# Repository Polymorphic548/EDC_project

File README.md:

# Diode-Compensated Current Mirror PCB

A single-sided PCB containing two independent, diode-compensated 2N3904 current mirrors. This repository includes the original LTspice circuit, KiCad schematic and layout, assembly drawings, and matched Gerber and drill files.

Each circuit has a power connector and three voltage-measurement headers: across the load and across each transistor's base and emitter.

| Specification | Design |
|---|---|
| Panel size / thickness | 150 x 100 mm / 1.7 mm |
| Circuits | Two electrically isolated copies, A and B |
| Copper | Single-sided, B.Cu |
| Track width / configured minimum clearance | 0.6 mm / 0.8 mm |
| Supply | 9.8 V DC per circuit |
| Assembly | Through-hole; 36 footprints including eight 2-pin headers |
| Header pitch | 2.54 mm |
| Adjustment resistor | Fixed 120 ohm; no trimmer |
| Software | KiCad 10.0.7 or later |

The saved design and exports pass the recorded CAD and geometry checks. **The rectangular-pad export still requires confirmation in the lab's CopperCAM installation.** Physical circuit performance has not been measured.

## Open the design

1. Open [dual_current_mirror.kicad_pro](PCB%20layout/dual_current_mirror.kicad_pro) in KiCad.
2. Open [dual_current_mirror.kicad_pcb](PCB%20layout/dual_current_mirror.kicad_pcb) in PCB Editor.
3. Press **Alt+3** for the 3D Viewer.

The [single-circuit project](PCB%20layout/current_mirror.kicad_pro) is a reusable 78 x 67 mm unit. Use the **dual** project for the complete panel.

[Copper preview](PCB%20layout/previews/dual_panel_copper_review.png) | [Panel schematic PDF](PCB%20layout/previews/dual_panel_schematic.pdf)

The supplied KiCad screenshot below shows the current placement and routing before the rectangular-pad update. The generated drawing above shows the current pads.

## Circuit and components

The input passes through a 1 ohm resistor and a series 1N4007 diode. A Zener and two signal diodes provide the compensation network. Each transistor has a 22 ohm emitter resistor, and the output drives a 1 kohm load. The LTspice parameterized resistor RV1 is implemented as fixed R7/R107, nominally 120 ohm.

| Copy A | Copy B | Component / value |
|---|---|---|
| R1 | R101 | 1 ohm, 1/4 W input resistor |
| R2 | R102 | 662 ohm, 1/4 W |
| R3 | R103 | 1 kohm, 1/4 W |
| R4, R5 | R104, R105 | 22 ohm, 1/4 W emitter resistors |
| R6 | R106 | 1 kohm, 1/4 W load |
| R7 | R107 | Fixed 120 ohm, 1/4 W |
| D1, D2 | D101, D102 | 1N4148 |
| D3 | D103 | BZX55C5V1, 5.1 V Zener |
| D4 | D104 | 1N4007 |
| Q1, Q2 | Q101, Q102 | 2N3904 |
| C1 | C101 | 1.33 nF, at least 25 V |
| J1-J4 | J101-J104 | Four 1x2 male headers, 2.54 mm pitch |

See the [panel BOM](PCB%20layout/panel_BOM.csv) for the complete assembly list. Two populated circuits require two sets of parts and eight headers total. R1 is a resistor, not a fuse.

The original nominal 120 ohm resistor measured 117.6 ohm; measure the second circuit's resistor separately. The supplied LTspice results report approximately **4.625 mA at 25 degrees C** and **4.667 mA at 75 degrees C** with RV=117.6 ohm. These are source simulation results, not PCB measurements.

## Power and measurements

| Connection | Copy A | Copy B | Pin 1: positive / red | Pin 2: negative / black |
|---|---|---|---|---|
| Power input | J1 | J101 | VIN, +9.8 V | GND |
| Load voltage | J2 | J102 | VCC | OUT |
| First transistor VBE | J3 | J103 | BASE | E1 |
| Second transistor VBE | J4 | J104 | BASE | E2 |

Use **DC voltage mode**, with meter leads in COM and V/ohm. The circuit operates normally without a meter. These connectors must not be fitted with shorting caps.

VCC is the internal supply after the input resistor and diode. E1 and E2 are separate emitter nodes above their 22 ohm resistors; neither is ground. Copy B's transistors are Q101 and Q102.

Calculate output current using `Iout = Vload / Rload`. With a 1 kohm load, 5.00 V corresponds to 5.00 mA.

The circuits share no PCB nets, including ground. A common external supply or common-ground instrument can connect them externally.

## Fabrication

Use [dual_panel_machine_files.zip](PCB%20layout/fabrication/dual_panel_machine_files.zip) for the lab handoff. The [rectangle-pad package](PCB%20layout/fabrication/dual_panel_coppercam_rectangles.zip) contains identical files under a distinct name for a fresh CopperCAM import.

| File inside the package | Purpose |
|---|---|
| `dual_current_mirror-B_Cu.gbr` | Copper to retain; the only copper layer |
| `dual_current_mirror.drl` | Excellon drill locations and sizes |
| `dual_current_mirror-Edge_Cuts.gbr` | Optional outer 150 x 100 mm outline |
| `dual_current_mirror-Centre_Cut.gbr` | Optional straight centre separation line |

The package also contains a drill map, tool report, setup data, verification results and checksums. All geometry uses millimetres and a shared absolute origin. Apply fixture mirroring or positioning consistently to all layers. Through-hole pads may appear on F.Cu in KiCad, but only the **bottom copper pattern** is fabricated.

Extract into a fresh folder and open the copper Gerber in a new CopperCAM circuit. Before calculating contours, confirm that all three rectangular pads on each of the four transistors are visible. Import the drill file and verify that every hole aligns with its pad; the lab previously achieved registration using layers 1 and 5. Inspect the calculated isolation paths before machining. The copper export uses only standard circle and rectangle pad apertures.

### Centre separation

The optional centreline runs at **x=75 mm** across the panel. A centred 0.8 mm cutter leaves nominal **74.6 x 100 mm** halves without outer trimming.

[Centre-cut setup data](PCB%20layout/centre_cut_setup.json) records a **Roland monoFab SRM-20**, 1.7 mm board, 0.8 mm cutting diameter and maximum 0.4 mm depth per pass. **No executable cutting program is included.** The operator must confirm feeds, spindle speed, safe Z, zero reference, cutter suitability, breakthrough allowance, work holding and output format. Secure both halves and complete isolation and drilling before separation.

### Printed masks

[Unmirrored copper PDF](PCB%20layout/fabrication/dual_panel_BCu_unmirrored_1to1.pdf) | [Mirrored copper PDF](PCB%20layout/fabrication/dual_panel_BCu_mirrored_1to1.pdf)

For transfer or photoresist fabrication, confirm orientation and exposure polarity with the lab. Print at **100% / Actual Size** and measure the **50 mm calibration line**. Black denotes copper to retain. Transfer only the board area; calibration marks sit outside it. Assembly and review drawings are not fabrication masks.

## Assembly

Fit components on the face opposite the copper and solder on the copper side. There is no solder mask; use controlled amounts of flux-cored solder and inspect nearby joints for bridges.

- Verify the actual transistor manufacturer's pinout. CAD numbering is **1=emitter, 2=base, 3=collector**.
- All transistor and header pads are rectangular: **pad shape does not identify pin 1**. Follow numbering and assembly labels.
- Confirm physical fit: resistor pitch 7.62 mm, capacitor pitch 5 mm, transistor and header pitch 2.54 mm.
- Header holes are 1.0 mm; transistor holes are 0.8 mm. The panel also has 1.1 mm diode holes.
- Check diode polarity and power-connector orientation before applying power.

## Repository guide

| Location | Contents |
|---|---|
| [schematics/](schematics/) | Original LTspice schematic and related source files |
| [PCB layout/](PCB%20layout/README.md) | KiCad projects, BOMs and technical documentation |
| [Project.pretty/](PCB%20layout/Project.pretty/) | Shared project-local footprints |
| [previews/](PCB%20layout/previews/) | Assembly, schematic and copper review drawings |
| [fabrication/](PCB%20layout/fabrication/) | Machine packages and 1:1 masks |
| [reports/](PCB%20layout/reports/) | CAD checks, geometry audits and revision records |
| [scripts/](PCB%20layout/scripts/) | Design generation, export and verification utilities |

Recorded checks report zero ERC/DRC violations, zero unconnected items and zero schematic-parity issues for both projects under their configured rules. Independent audits verify isolated A/B nets, header connections, pad-to-netlist agreement and matching export geometry: **76 pads, 76 holes and 100 panel track segments**.

[Panel audit](PCB%20layout/reports/panel_audit.json) | [Export verification](PCB%20layout/fabrication/machine_files/verification.json) | [Pad audit](PCB%20layout/reports/coppercam_pads.json)

These checks establish saved-file consistency. Lab import, toolpaths, machining and physical circuit performance require verification on the actual equipment. Earlier revision records remain in `reports/`.

## License

This project is licensed under the [MIT License](LICENSE).

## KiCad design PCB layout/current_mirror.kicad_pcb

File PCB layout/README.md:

# PCB Design and Manufacturing Guide

This directory contains the KiCad implementation of the diode-compensated current mirror: a reusable circuit and a 150 x 100 mm panel containing two isolated copies. See the [project overview](../README.md) for component values and measurement instructions.

## Projects and previews

| Project | Purpose | Board size |
|---|---|---|
| [dual_current_mirror.kicad_pro](dual_current_mirror.kicad_pro) | Complete panel for fabrication | 150 x 100 mm |
| [current_mirror.kicad_pro](current_mirror.kicad_pro) | Reusable single circuit | 78 x 67 mm |

Open with **KiCad 10.0.7 or later**. Open the PCB in PCB Editor and press **Alt+3** for 3D. Both projects use [Project.pretty](Project.pretty/) through the supplied `fp-lib-table`. Reopen files from disk after external edits to avoid saving an older editor copy over them.

[Assembly PDF](previews/dual_panel_assembly.pdf) | [Copper review](previews/dual_panel_copper_review.png) | [Schematic PDF](previews/dual_panel_schematic.pdf)

The supplied screenshot shows the current placement and routing before the rectangular-pad update. The generated previews show the current pad outlines.

## Board construction

| Parameter | Specification |
|---|---|
| Physical copper / thickness | Single-sided B.Cu / 1.7 mm |
| Tracks | 0.6 mm; horizontal, vertical and 45 degrees sections |
| Configured minimum different-net clearance | 0.8 mm |
| Vias / jumpers / pours | None |
| Footprints / nets | 36 / 24 |
| Pad shapes | 36 rectangular, 40 circular |
| Holes | 56 x 0.8 mm; 16 x 1.0 mm; 4 x 1.1 mm |

Each unit is rotated 90 degrees, occupying 67 x 78 mm. Copy A's unit rectangle spans x=5.5-72.5 mm, y=11-89 mm; copy B spans x=77.5-144.5 mm, y=11-89 mm. The unit rectangles have a 5 mm gap.

Copy B adds 100 to the references: Q1 -> Q101, J1 -> J101, etc. All A/B nets are separate, including ground. Shared external supplies or instruments can connect them externally.

Only the outer boundary is on Edge.Cuts. The centre separation line is on User.1 and exports separately. Through-hole pads appear on both copper layers in KiCad's data model; all routing and fabrication copper artwork are B.Cu.

## Headers and footprints

All eight connectors are 1x2 male headers, 2.54 mm pitch. Use female jumper leads for power and instruments.

| Function | Copy A / B | Pin 1 | Pin 2 |
|---|---|---|---|
| 9.8 V power | J1 / J101 | VIN | GND |
| Load voltage | J2 / J102 | VCC | OUT |
| First transistor VBE | J3 / J103 | BASE | E1 |
| Second transistor VBE | J4 / J104 | BASE | E2 |

Use DC volts with red on pin 1 and black on pin 2. Emitters are separate nodes above their 22 ohm resistors. Do not fit shorting caps.

In the single-unit orientation, transistor pads are 1.7 x 2.4 mm with 0.8 mm holes; header pads are 2.4 x 1.7 mm with 1.0 mm holes. Both have 2.54 mm pitch and a 0.84 mm adjacent-pad gap. Panel rotation swaps the X/Y dimensions.

All transistor and header pads are rectangular. Identify pins by numbering and assembly labels, not pad shape. Transistor numbering is **1=E, 2=B, 3=C**; check the actual manufacturer's pinout. Confirm lead forming, resistor pitch of 7.62 mm and C1's assumed 5 mm lead spacing before fabrication.

[Panel BOM](panel_BOM.csv) | [Panel component/net data](panel_components.json) | [Unit BOM](BOM.csv)

## Machine handoff

Use [dual_panel_machine_files.zip](fabrication/dual_panel_machine_files.zip). The separately named [dual_panel_coppercam_rectangles.zip](fabrication/dual_panel_coppercam_rectangles.zip) contains identical files for the fresh import check.

| File | Import as |
|---|---|
| `dual_current_mirror-B_Cu.gbr` | Copper to retain |
| `dual_current_mirror.drl` | Excellon drilling data |
| `dual_current_mirror-Edge_Cuts.gbr` | Optional outer outline |
| `dual_current_mirror-Centre_Cut.gbr` | Optional centreline separation cut |

All files use millimetres, absolute coordinates and a shared unmirrored origin. Apply machine-side positioning or mirroring consistently to copper, drilling and cutting. No front-copper file is required. These files are CAM inputs; the operator generates executable machine output.

For CopperCAM:

1. Extract into a fresh folder and start a new circuit with the copper Gerber.
2. Before calculating contours, verify all three pads on each of Q1, Q2, Q101 and Q102, plus the header and diode pads.
3. Import the drill file and check every hole against its pad centre. The lab previously resolved registration using layers 1 and 5.
4. Inspect the calculated isolation paths for intact pads and connections before machining.

The export contains only standard circle/rectangle pad apertures, without oval pads, rounded rectangles, aperture macros or filled pad regions. **The rectangular-pad version still requires import confirmation in the lab's CopperCAM installation.**

### Centre separation

The centre-cut file contains one straight line at x=75 mm, y=0-100 mm in board coordinates. Import it as a separate centreline cutting operation, preserving alignment with the copper. It is not a closed outline or copper artwork.

[centre_cut_setup.json](centre_cut_setup.json) records the SRM-20, 1.7 mm board, 0.8 mm cutter diameter and maximum 0.4 mm pass depth. Nominal planning depths to board bottom are 0.4, 0.8, 1.2, 1.6 and 1.7 mm.

No executable RML/G-code or tabs are included. The operator must confirm feeds, spindle speed, safe Z, Z-zero, cutter type/usable length, holding, breakthrough allowance and output format. Secure both halves over a suitable sacrificial board and complete isolation and drilling before separation. A centred 0.8 mm kerf leaves nominal 74.6 x 100 mm halves without outer trimming.

### Printed masks

[Unmirrored 1:1 PDF](fabrication/dual_panel_BCu_unmirrored_1to1.pdf) | [Mirrored 1:1 PDF](fabrication/dual_panel_BCu_mirrored_1to1.pdf)

These contain B.Cu only; black denotes copper to keep. Confirm transfer orientation and exposure polarity with the lab. Print at Actual Size / 100%, measure the 50 mm calibration line and transfer only the board area. Review drawings are not masks. See [printing instructions](fabrication/PRINTING_README.md).

## Verification records

Recorded native checks report zero ERC/DRC violations, zero unconnected items and zero schematic-parity issues under the configured rules. Independent audits cover component values, netlist-to-pad agreement, header roles, unique identifiers, isolation, clearances and all 76 pad/drill locations.

| Record | Scope |
|---|---|
| [Panel audit](reports/panel_audit.json) | Dimensions, isolated nets and component mapping |
| [Panel ERC](reports/panel_erc.json) / [DRC](reports/panel_drc.json) | Native KiCad checks |
| [Source connectivity](reports/source_connectivity.json) | LTspice topology comparison |
| [Solder clearance](reports/solder_clearance.json) | Pad gaps and annular copper |
| [Pad audit](reports/coppercam_pads.json) | Rectangular transistor pads and Gerber apertures |
| [Export verification](fabrication/machine_files/verification.json) | Copper/drill geometry and cutting files |
| [Panel hashes](reports/panel_sha256.json) | Design and print-artifact integrity |

The reports establish saved-file consistency, not machining or electrical performance. Original LTspice files are preserved. The PCB uses fixed nominal 120 ohm resistors; the original source used RV=117.6 ohm. Earlier revision reports and trimmer templates are historical records.

## Maintenance

The [scripts](scripts/) include generators, routing, exports and checks. KiCad's bundled Python supplies `pcbnew`; PNG preview rendering uses regular Python with PyMuPDF. Some source checks also read installed LTspice symbols.

Treat the saved CAD files as the handoff design. Back up manual edits before running generators or the router: they rebuild geometry and may replace the saved placement or routing. After CAD changes, regenerate the relevant netlists, ERC/DRC/parity reports, audits, previews and manufacturing exports before packaging a new ZIP.

`export_machine_files.ps1` exports machine files; `check_machine_files.py` compares them with the board and writes verification/checksum records. Package those checked files together. Documentation-only edits do not require regeneration of manufacturing artifacts.

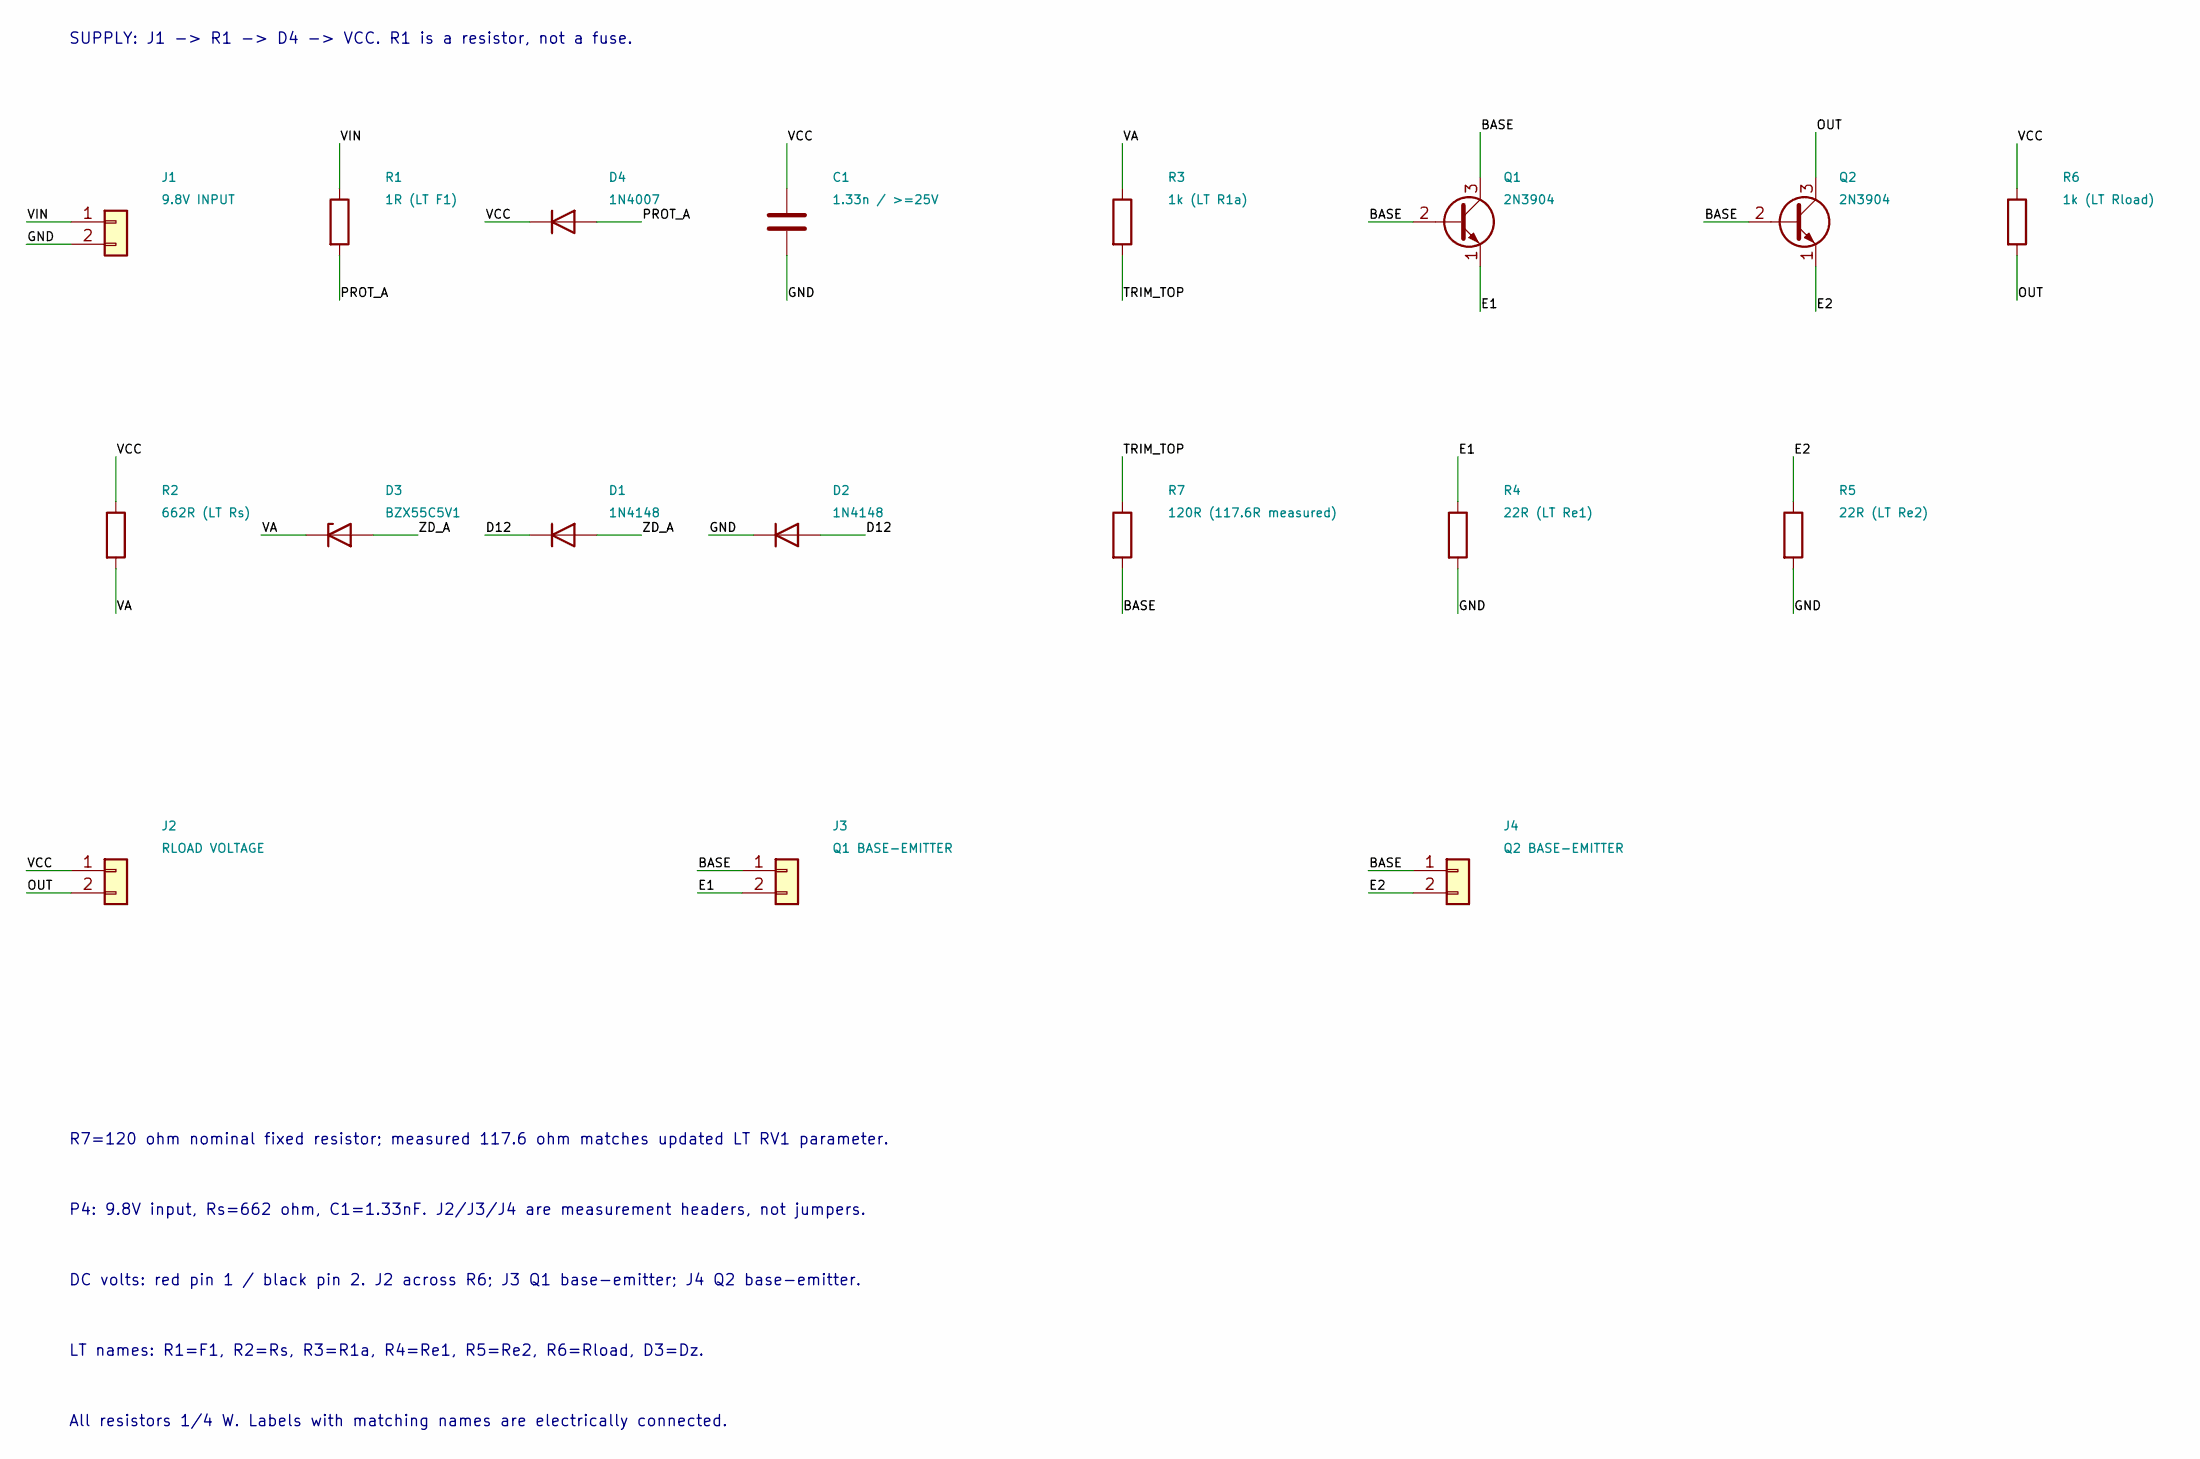
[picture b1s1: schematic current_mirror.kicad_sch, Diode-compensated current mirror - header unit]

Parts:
C1: 1.33n / >=25V; C1_ETCH
D1: 1N4148; D1_ETCH
D2: 1N4148; D2_ETCH
D3: BZX55C5V1; D3_ETCH
D4: 1N4007; D4_ETCH
J1: 9.8V INPUT; J1_ETCH
J2: RLOAD VOLTAGE; J2_ETCH
J3: Q1 BASE-EMITTER; J3_ETCH
J4: Q2 BASE-EMITTER; J4_ETCH
Q1: 2N3904; Q1_ETCH
Q2: 2N3904; Q2_ETCH
R1: 1R (LT F1); R1_ETCH
R2: 662R (LT Rs); R2_ETCH
R3: 1k (LT R1a); R3_ETCH
R4: 22R (LT Re1); R4_ETCH
R5: 22R (LT Re2); R5_ETCH
R6: 1k (LT Rload); R6_ETCH
R7: 120R (117.6R measured); R7_ETCH

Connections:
/BASE: J3.1, J4.1, Q1.2 (B), Q1.3 (C), Q2.2 (B), R7.2
/D12: D1.1 (K), D2.2 (A)
/E1: J3.2, Q1.1 (E), R4.1
/E2: J4.2, Q2.1 (E), R5.1
/GND: C1.2, D2.1 (K), J1.2, R4.2, R5.2
/OUT: J2.2, Q2.3 (C), R6.2
/PROT_A: D4.2 (A), R1.2
/TRIM_TOP: R3.2, R7.1
/VA: D3.1 (K), R2.2, R3.1
/VCC: C1.1, D4.1 (K), J2.1, R2.1, R6.1
/VIN: J1.1, R1.1
/ZD_A: D1.2 (A), D3.2 (A)

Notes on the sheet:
SUPPLY: J1 -> R1 -> D4 -> VCC. R1 is a resistor, not a fuse.
R7=120 ohm nominal fixed resistor; measured 117.6 ohm matches updated LT RV1 parameter.
P4: 9.8V input, Rs=662 ohm, C1=1.33nF. J2/J3/J4 are measurement headers, not jumpers.
DC volts: red pin 1 / black pin 2. J2 across R6; J3 Q1 base-emitter; J4 Q2 base-emitter.
LT names: R1=F1, R2=Rs, R3=R1a, R4=Re1, R5=Re2, R6=Rload, D3=Dz.
All resistors 1/4 W. Labels with matching names are electrically connected.

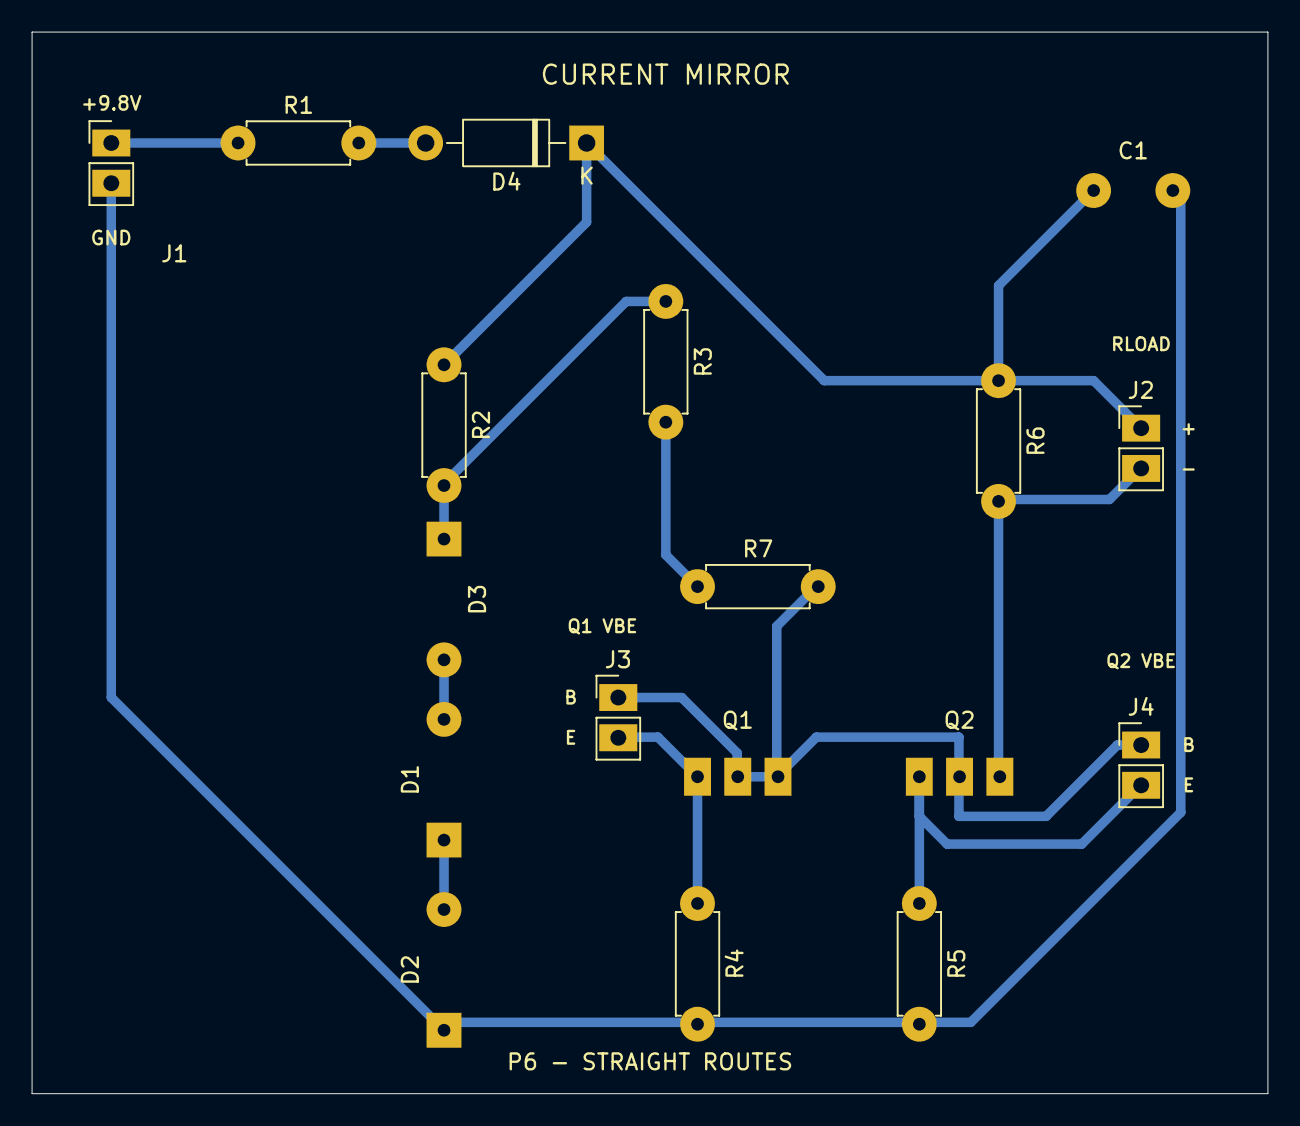
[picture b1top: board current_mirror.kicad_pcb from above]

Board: 2 copper layers, 78.0 x 67.0 mm, 18 parts (0 on the bottom side), 12 nets.

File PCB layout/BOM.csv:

Reference,Value,Footprint,Status
J1,9.8V INPUT,Project:J1_ETCH,package assumption - confirm physical part
R1,1R (LT F1),Project:R1_ETCH,package assumption - confirm physical part
D4,1N4007,Project:D4_ETCH,package assumption - confirm physical part
C1,1.33n / >=25V,Project:C1_ETCH,package assumption - confirm physical part
R2,662R (LT Rs),Project:R2_ETCH,package assumption - confirm physical part
D3,BZX55C5V1,Project:D3_ETCH,package assumption - confirm physical part
D1,1N4148,Project:D1_ETCH,package assumption - confirm physical part
D2,1N4148,Project:D2_ETCH,package assumption - confirm physical part
R3,1k (LT R1a),Project:R3_ETCH,package assumption - confirm physical part
R7,120R (117.6R measured),Project:R7_ETCH,package assumption - confirm physical part
Q1,2N3904,Project:Q1_ETCH,package assumption - confirm physical part
Q2,2N3904,Project:Q2_ETCH,package assumption - confirm physical part
R4,22R (LT Re1),Project:R4_ETCH,package assumption - confirm physical part
R5,22R (LT Re2),Project:R5_ETCH,package assumption - confirm physical part
R6,1k (LT Rload),Project:R6_ETCH,package assumption - confirm physical part
J2,RLOAD VOLTAGE,Project:J2_ETCH,package assumption - confirm physical part
J3,Q1 BASE-EMITTER,Project:J3_ETCH,package assumption - confirm physical part
J4,Q2 BASE-EMITTER,Project:J4_ETCH,package assumption - confirm physical part

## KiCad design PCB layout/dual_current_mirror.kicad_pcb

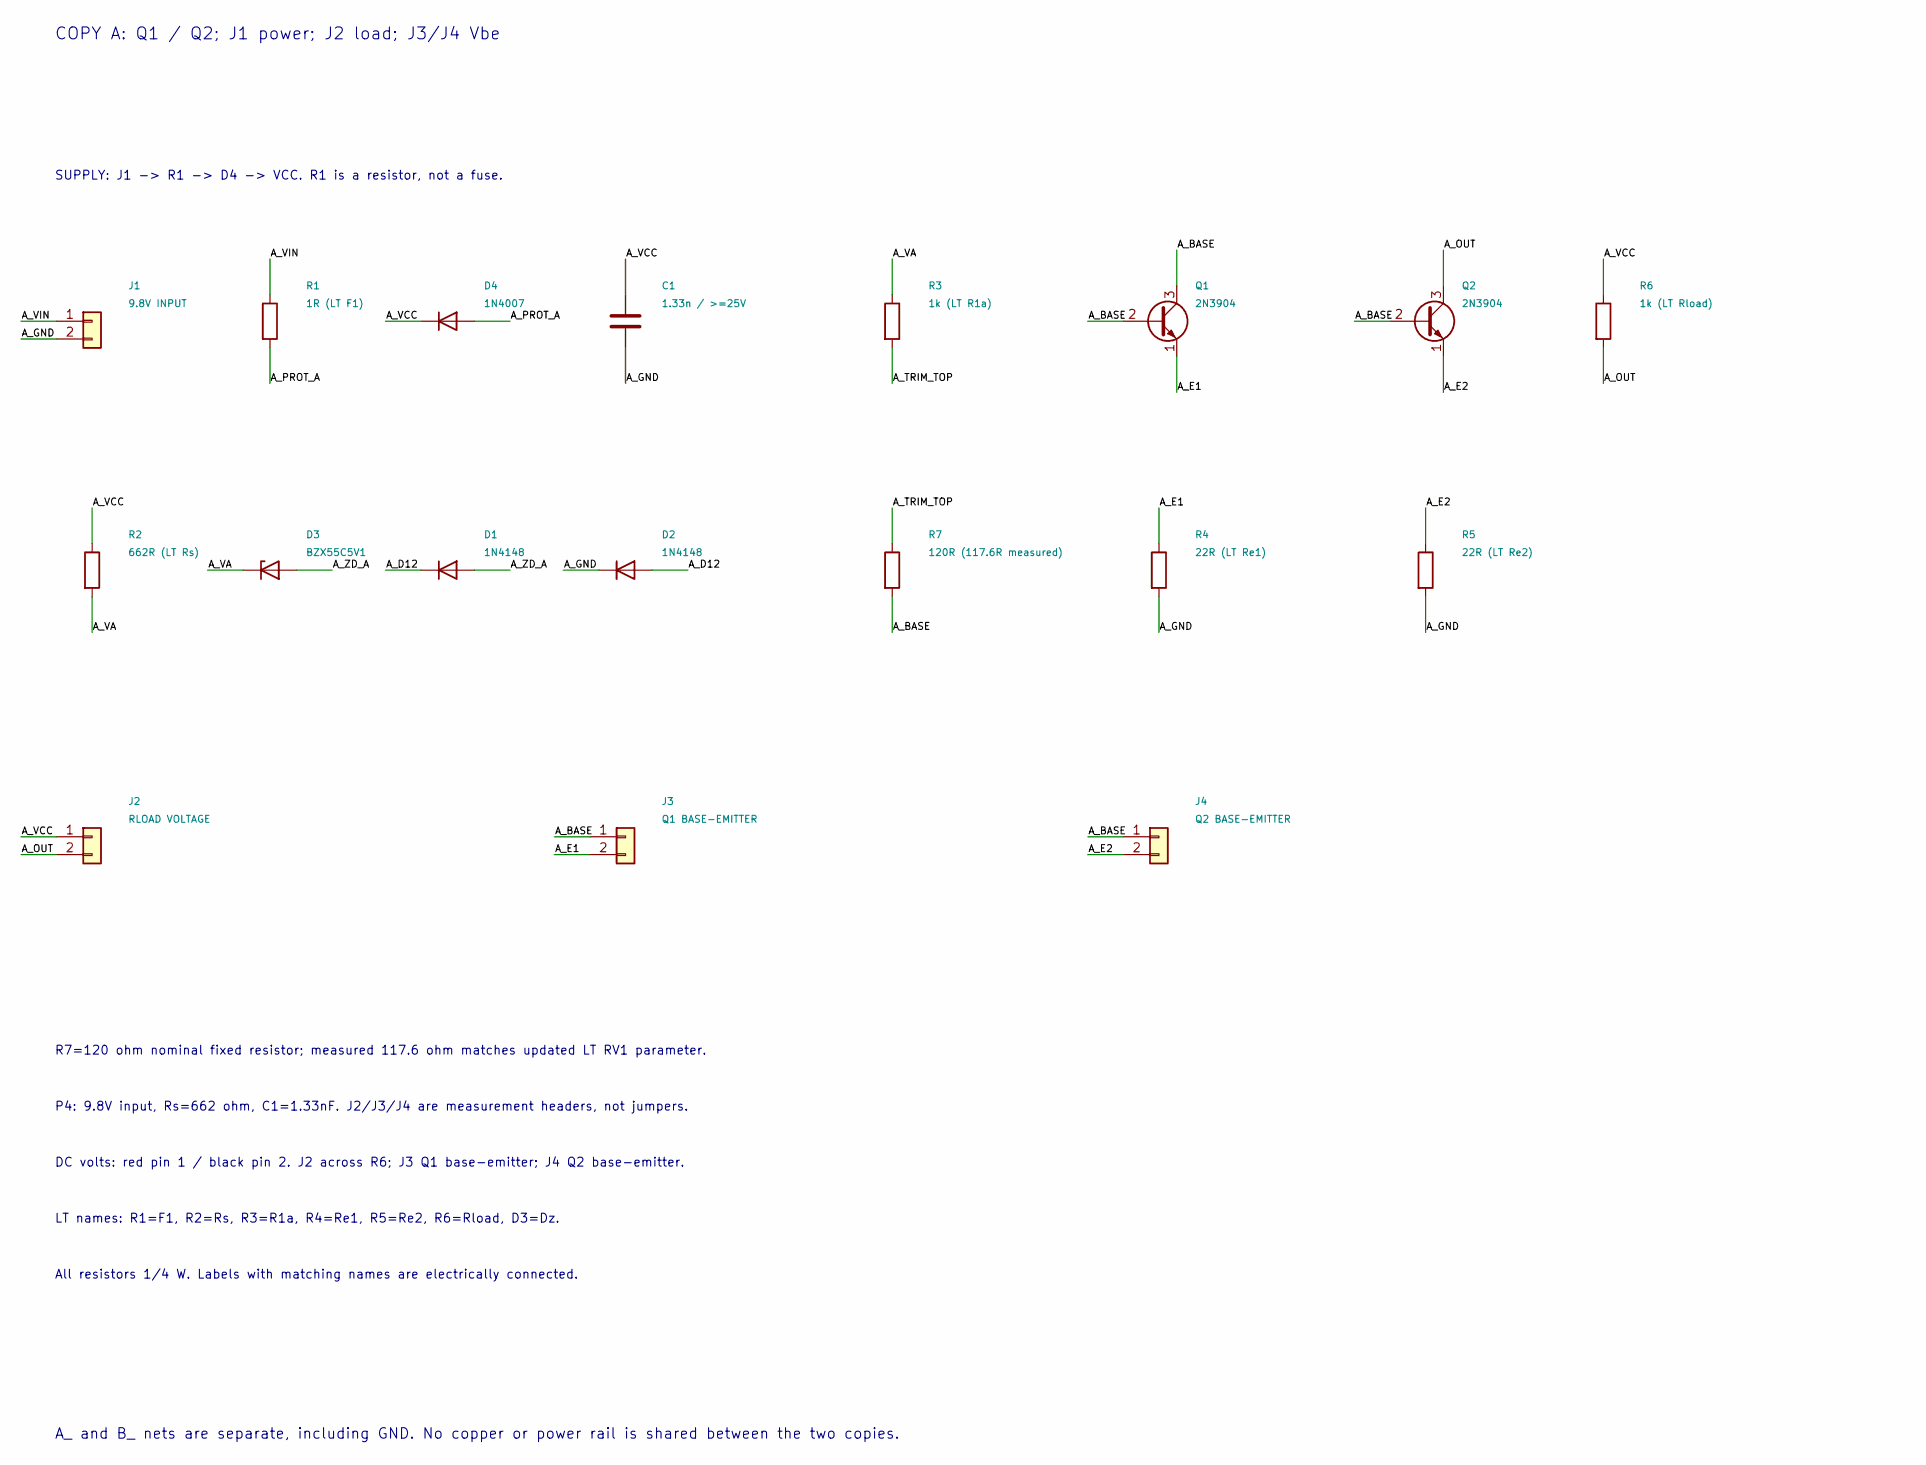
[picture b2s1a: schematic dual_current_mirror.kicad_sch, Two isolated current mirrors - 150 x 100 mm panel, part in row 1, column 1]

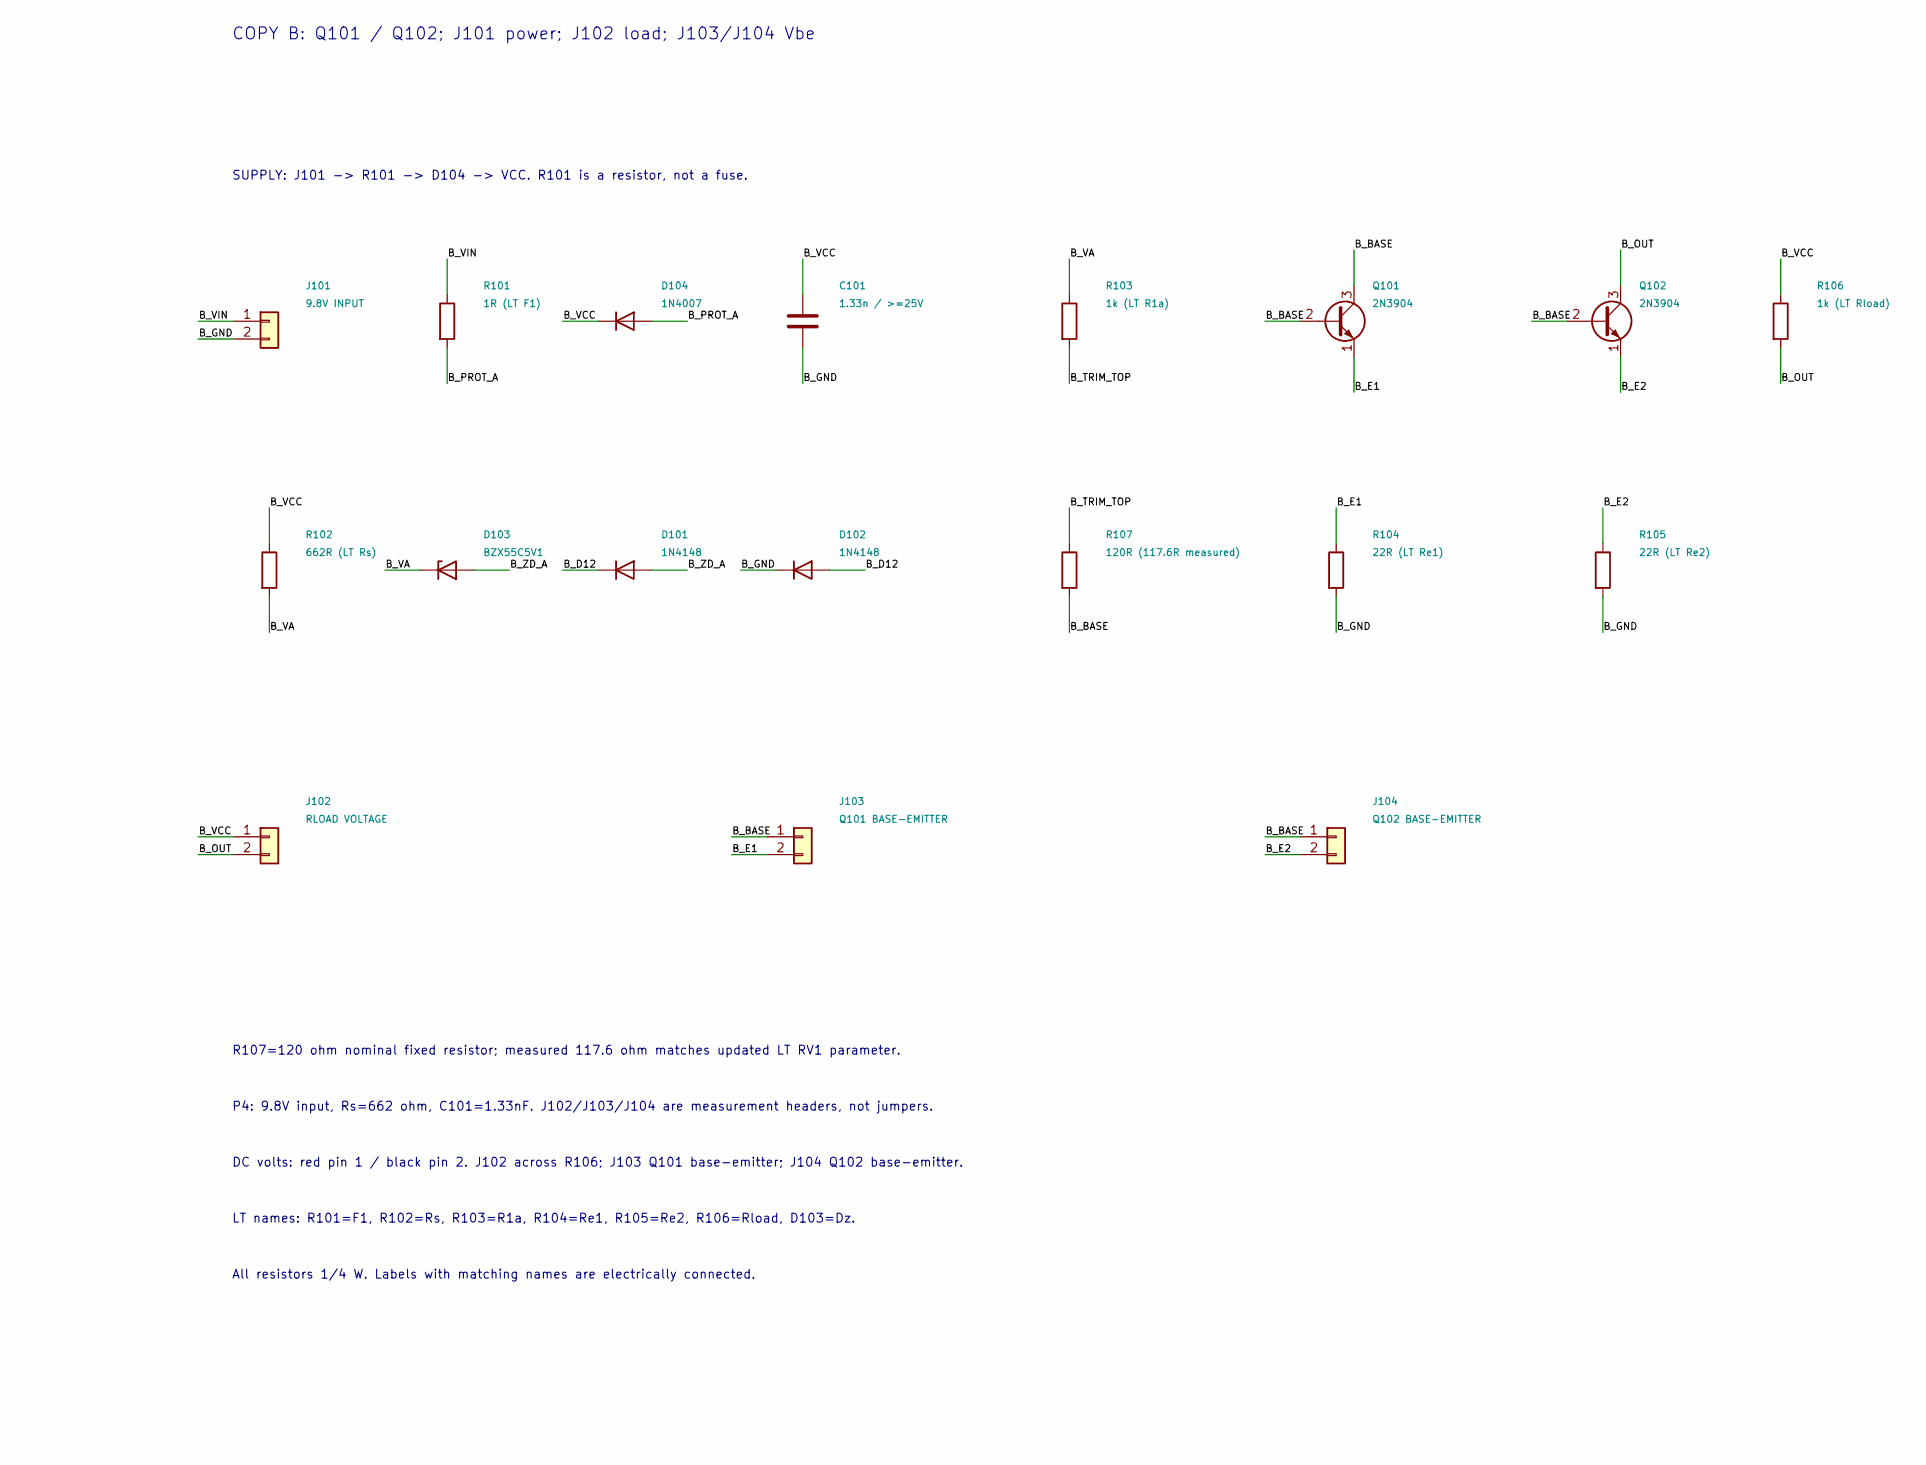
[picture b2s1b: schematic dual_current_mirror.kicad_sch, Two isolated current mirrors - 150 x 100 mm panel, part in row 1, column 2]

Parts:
C1, C101: 1.33n / >=25V; C1_ETCH
D1, D101: 1N4148; D1_ETCH
D2, D102: 1N4148; D2_ETCH
D3, D103: BZX55C5V1; D3_ETCH
D4, D104: 1N4007; D4_ETCH
J1, J101: 9.8V INPUT; J1_ETCH
J2, J102: RLOAD VOLTAGE; J2_ETCH
J3: Q1 BASE-EMITTER; J3_ETCH
J4: Q2 BASE-EMITTER; J4_ETCH
J103: Q101 BASE-EMITTER; J3_ETCH
J104: Q102 BASE-EMITTER; J4_ETCH
Q1, Q101: 2N3904; Q1_ETCH
Q2, Q102: 2N3904; Q2_ETCH
R1, R101: 1R (LT F1); R1_ETCH
R2, R102: 662R (LT Rs); R2_ETCH
R3, R103: 1k (LT R1a); R3_ETCH
R4, R104: 22R (LT Re1); R4_ETCH
R5, R105: 22R (LT Re2); R5_ETCH
R6, R106: 1k (LT Rload); R6_ETCH
R7, R107: 120R (117.6R measured); R7_ETCH

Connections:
/A_BASE: J3.1, J4.1, Q1.2 (B), Q1.3 (C), Q2.2 (B), R7.2
/A_D12: D1.1 (K), D2.2 (A)
/A_E1: J3.2, Q1.1 (E), R4.1
/A_E2: J4.2, Q2.1 (E), R5.1
/A_GND: C1.2, D2.1 (K), J1.2, R4.2, R5.2
/A_OUT: J2.2, Q2.3 (C), R6.2
/A_PROT_A: D4.2 (A), R1.2
/A_TRIM_TOP: R3.2, R7.1
/A_VA: D3.1 (K), R2.2, R3.1
/A_VCC: C1.1, D4.1 (K), J2.1, R2.1, R6.1
/A_VIN: J1.1, R1.1
/A_ZD_A: D1.2 (A), D3.2 (A)
/B_BASE: J103.1, J104.1, Q101.2 (B), Q101.3 (C), Q102.2 (B), R107.2
/B_D12: D101.1 (K), D102.2 (A)
/B_E1: J103.2, Q101.1 (E), R104.1
/B_E2: J104.2, Q102.1 (E), R105.1
/B_GND: C101.2, D102.1 (K), J101.2, R104.2, R105.2
/B_OUT: J102.2, Q102.3 (C), R106.2
/B_PROT_A: D104.2 (A), R101.2
/B_TRIM_TOP: R103.2, R107.1
/B_VA: D103.1 (K), R102.2, R103.1
/B_VCC: C101.1, D104.1 (K), J102.1, R102.1, R106.1
/B_VIN: J101.1, R101.1
/B_ZD_A: D101.2 (A), D103.2 (A)

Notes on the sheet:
SUPPLY: J1 -> R1 -> D4 -> VCC. R1 is a resistor, not a fuse.
R7=120 ohm nominal fixed resistor; measured 117.6 ohm matches updated LT RV1 parameter.
P4: 9.8V input, Rs=662 ohm, C1=1.33nF. J2/J3/J4 are measurement headers, not jumpers.
DC volts: red pin 1 / black pin 2. J2 across R6; J3 Q1 base-emitter; J4 Q2 base-emitter.
LT names: R1=F1, R2=Rs, R3=R1a, R4=Re1, R5=Re2, R6=Rload, D3=Dz.
All resistors 1/4 W. Labels with matching names are electrically connected.
COPY A: Q1 / Q2; J1 power; J2 load; J3/J4 Vbe
SUPPLY: J101 -> R101 -> D104 -> VCC. R101 is a resistor, not a fuse.
R107=120 ohm nominal fixed resistor; measured 117.6 ohm matches updated LT RV1 parameter.
P4: 9.8V input, Rs=662 ohm, C101=1.33nF. J102/J103/J104 are measurement headers, not jumpers.
DC volts: red pin 1 / black pin 2. J102 across R106; J103 Q101 base-emitter; J104 Q102 base-emitter.
LT names: R101=F1, R102=Rs, R103=R1a, R104=Re1, R105=Re2, R106=Rload, D103=Dz.
COPY B: Q101 / Q102; J101 power; J102 load; J103/J104 Vbe
A_ and B_ nets are separate, including GND. No copper or power rail is shared between the two copies.

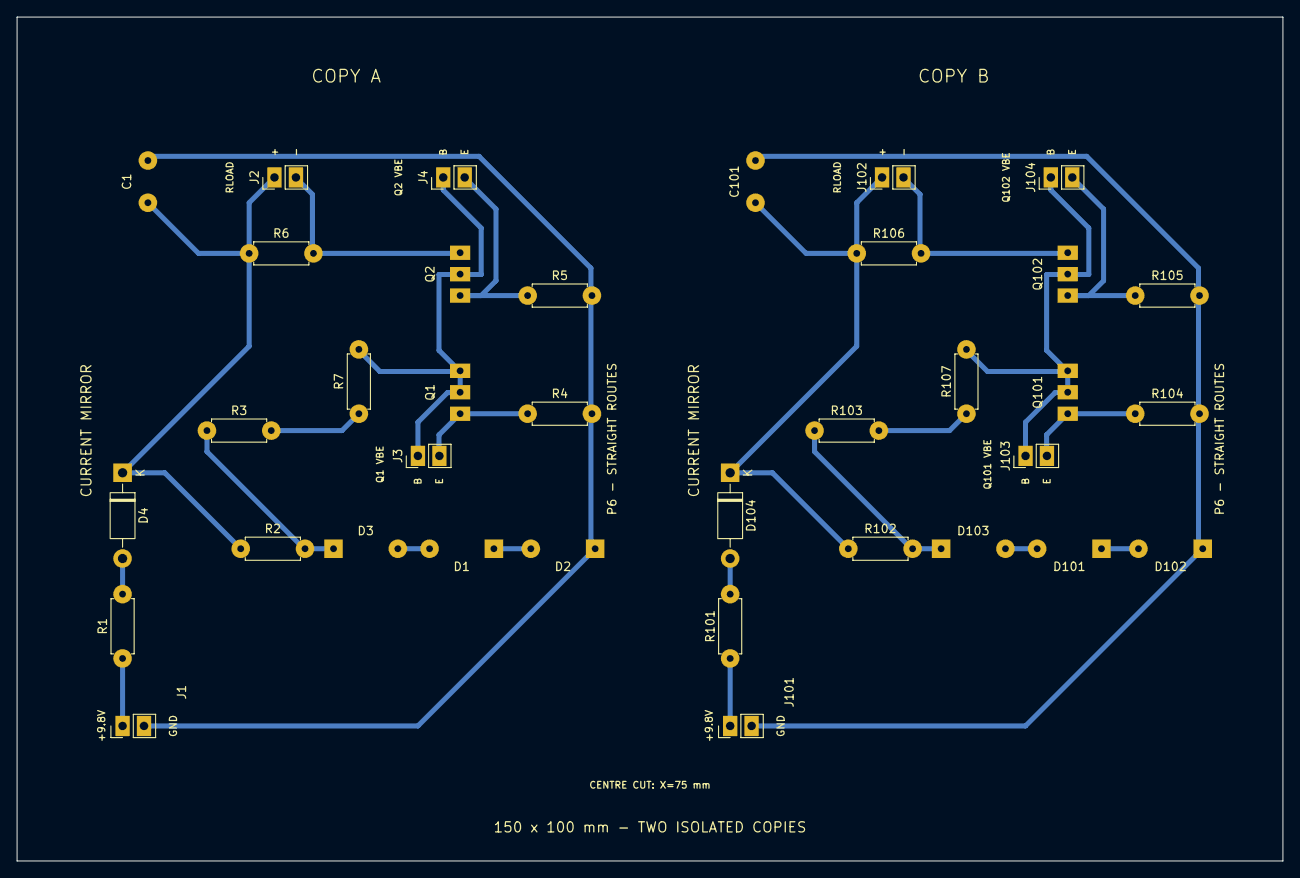
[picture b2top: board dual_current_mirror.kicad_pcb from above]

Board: 2 copper layers, 150.0 x 100.0 mm, 36 parts (0 on the bottom side), 24 nets.

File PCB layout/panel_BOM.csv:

Copy,Reference,Unit reference,Value,Notes
A,Q2,Q2,2N3904,
A,R1,R1,1R (LT F1),
A,R2,R2,662R (LT Rs),
A,D2,D2,1N4148,
A,C1,C1,1.33n / >=25V,
A,Q1,Q1,2N3904,
A,D1,D1,1N4148,
A,J2,J2,RLOAD VOLTAGE,
A,J4,J4,Q2 BASE-EMITTER,
A,J1,J1,9.8V INPUT,
A,D3,D3,BZX55C5V1,
A,R3,R3,1k (LT R1a),
A,R4,R4,22R (LT Re1),
A,R5,R5,22R (LT Re2),
A,J3,J3,Q1 BASE-EMITTER,
A,D4,D4,1N4007,
A,R6,R6,1k (LT Rload),
A,R7,R7,120R (117.6R measured),R7 measurement reported for original part only; measure each assembled copy separately
B,Q102,Q2,2N3904,
B,R101,R1,1R (LT F1),
B,R102,R2,662R (LT Rs),
B,D102,D2,1N4148,
B,C101,C1,1.33n / >=25V,
B,Q101,Q1,2N3904,
B,D101,D1,1N4148,
B,J102,J2,RLOAD VOLTAGE,
B,J104,J4,Q102 BASE-EMITTER,
B,J101,J1,9.8V INPUT,
B,D103,D3,BZX55C5V1,
B,R103,R3,1k (LT R1a),
B,R104,R4,22R (LT Re1),
B,R105,R5,22R (LT Re2),
B,J103,J3,Q101 BASE-EMITTER,
B,D104,D4,1N4007,
B,R106,R6,1k (LT Rload),
B,R107,R7,120R (117.6R measured),R7 measurement reported for original part only; measure each assembled copy separately
